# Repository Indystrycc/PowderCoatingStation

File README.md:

# PowderCoatingStation
Small and simple powder coating station with filters and light for small scale production.

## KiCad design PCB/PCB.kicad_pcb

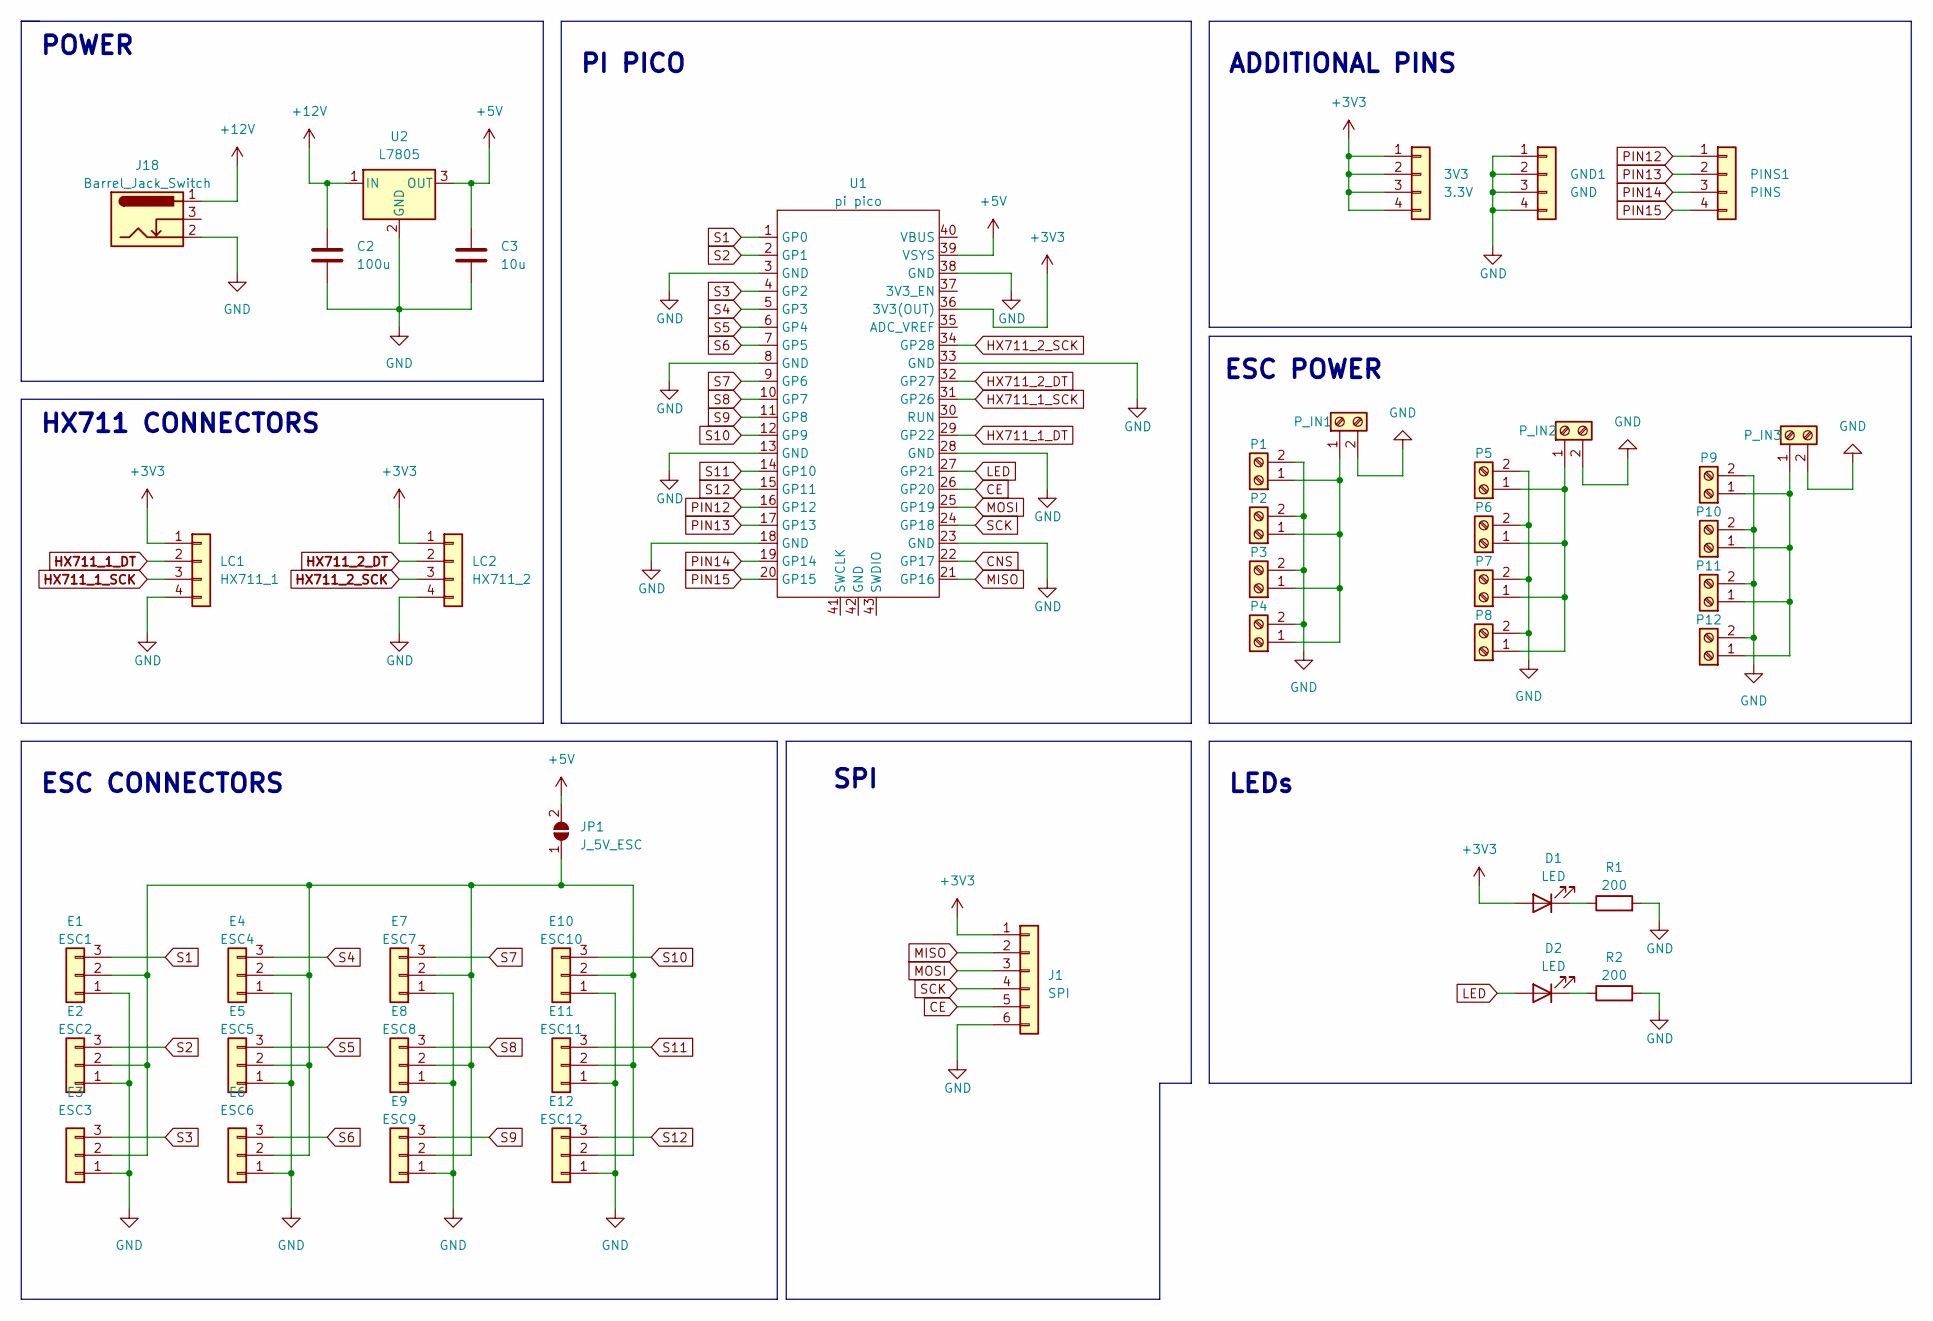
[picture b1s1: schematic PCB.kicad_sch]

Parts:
3V3: 3.3V; PinSocket_1x04_P2.54mm_Vertical
C2: 100u; C_Disc_D3.0mm_W2.0mm_P2.50mm
C3: 10u; C_Disc_D3.0mm_W2.0mm_P2.50mm
D1, D2: LED; LED_D5.0mm
E1: ESC1; PinSocket_1x03_P2.54mm_Vertical
E2: ESC2; PinSocket_1x03_P2.54mm_Vertical
E3: ESC3; PinSocket_1x03_P2.54mm_Vertical
E4: ESC4; PinSocket_1x03_P2.54mm_Vertical
E5: ESC5; PinSocket_1x03_P2.54mm_Vertical
E6: ESC6; PinSocket_1x03_P2.54mm_Vertical
E7: ESC7; PinSocket_1x03_P2.54mm_Vertical
E8: ESC8; PinSocket_1x03_P2.54mm_Vertical
E9: ESC9; PinSocket_1x03_P2.54mm_Vertical
E10: ESC10; PinSocket_1x03_P2.54mm_Vertical
E11: ESC11; PinSocket_1x03_P2.54mm_Vertical
E12: ESC12; PinSocket_1x03_P2.54mm_Vertical
GND1: GND; PinSocket_1x04_P2.54mm_Vertical
J1: SPI; PinSocket_1x06_P2.54mm_Vertical
J18: Barrel_Jack_Switch; BarrelJack_Horizontal
JP1: J_5V_ESC; SolderJumper-2_P1.3mm_Open_RoundedPad1.0x1.5mm
LC1: HX711_1; PinSocket_1x04_P2.54mm_Vertical
LC2: HX711_2; PinSocket_1x04_P2.54mm_Vertical
P1, P2, P3, P4, P5, P6, P7, P8, P9, P10, P11, P12: P1; TerminalBlock_bornier-2_P5.08mm
PINS1: PINS; PinSocket_1x04_P2.54mm_Vertical
P_IN1, P_IN2, P_IN3: P; TerminalBlock_bornier-2_P5.08mm
R1, R2: 200; R_0603_1608Metric_Pad0.98x0.95mm_HandSolder
U1: pi pico; raspberry pi pico
U2: L7805; TO-220-3_Vertical

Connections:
+3V3: 3V3.1, 3V3.2, 3V3.3, 3V3.4, D1.2 (A), J1.1, LC1.1, LC2.1, U1.36 (3V3(OUT))
CE: J1.5, U1.26 (GP20)
CNS: U1.22 (GP17)
GND: C2.2, E1.1, E2.1, E3.1, E4.1, E5.1, E6.1, E7.1, E8.1, E9.1, E10.1, E11.1, E12.1, GND1.1, GND1.2, GND1.3, GND1.4, J1.6, J18.2, LC1.4, LC2.4, P1.2, P2.2, P3.2, P4.2, P5.2, P6.2, P7.2, P8.2, P9.2, P10.2, P11.2, P12.2, P_IN1.2, P_IN2.2, P_IN3.2, R1.2, R2.2, U1.3 (GND), U1.8 (GND), U1.13 (GND), U1.18 (GND), U1.23 (GND), U1.28 (GND), U1.33 (GND), U1.38 (GND), U2.2 (GND); also elsewhere on the board
HX711_1_DT: LC1.2, U1.29 (GP22)
HX711_1_SCK: LC1.3, U1.31 (GP26)
HX711_2_DT: LC2.2, U1.32 (GP27)
HX711_2_SCK: LC2.3, U1.34 (GP28)
LED: D2.2 (A), U1.27 (GP21)
MISO: J1.2, U1.21 (GP16)
MOSI: J1.3, U1.25 (GP19)
unnamed: D1.1 (K), R1.1
unnamed: D2.1 (K), R2.1
unnamed: E1.2, E2.2, E3.2, E4.2, E5.2, E6.2, E7.2, E8.2, E9.2, E10.2, E11.2, E12.2, JP1.1 (A)
unnamed: P1.1, P2.1, P3.1, P4.1, P_IN1.1
unnamed: P5.1, P6.1, P7.1, P8.1, P_IN2.1
unnamed: P9.1, P10.1, P11.1, P12.1, P_IN3.1
PIN12: PINS1.1, U1.16 (GP12)
PIN13: PINS1.2, U1.17 (GP13)
PIN14: PINS1.3, U1.19 (GP14)
PIN15: PINS1.4, U1.20 (GP15)
S1: E1.3, U1.1 (GP0)
S2: E2.3, U1.2 (GP1)
S3: E3.3, U1.4 (GP2)
S4: E4.3, U1.5 (GP3)
S5: E5.3, U1.6 (GP4)
S6: E6.3, U1.7 (GP5)
S7: E7.3, U1.9 (GP6)
S8: E8.3, U1.10 (GP7)
S9: E9.3, U1.11 (GP8)
S10: E10.3, U1.12 (GP9)
S11: E11.3, U1.14 (GP10)
S12: E12.3, U1.15 (GP11)
SCK: J1.4, U1.24 (GP18)

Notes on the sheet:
ESC CONNECTORS
LEDs
ADDITIONAL PINS
SPI
ESC POWER
HX711 CONNECTORS
PI PICO
POWER

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
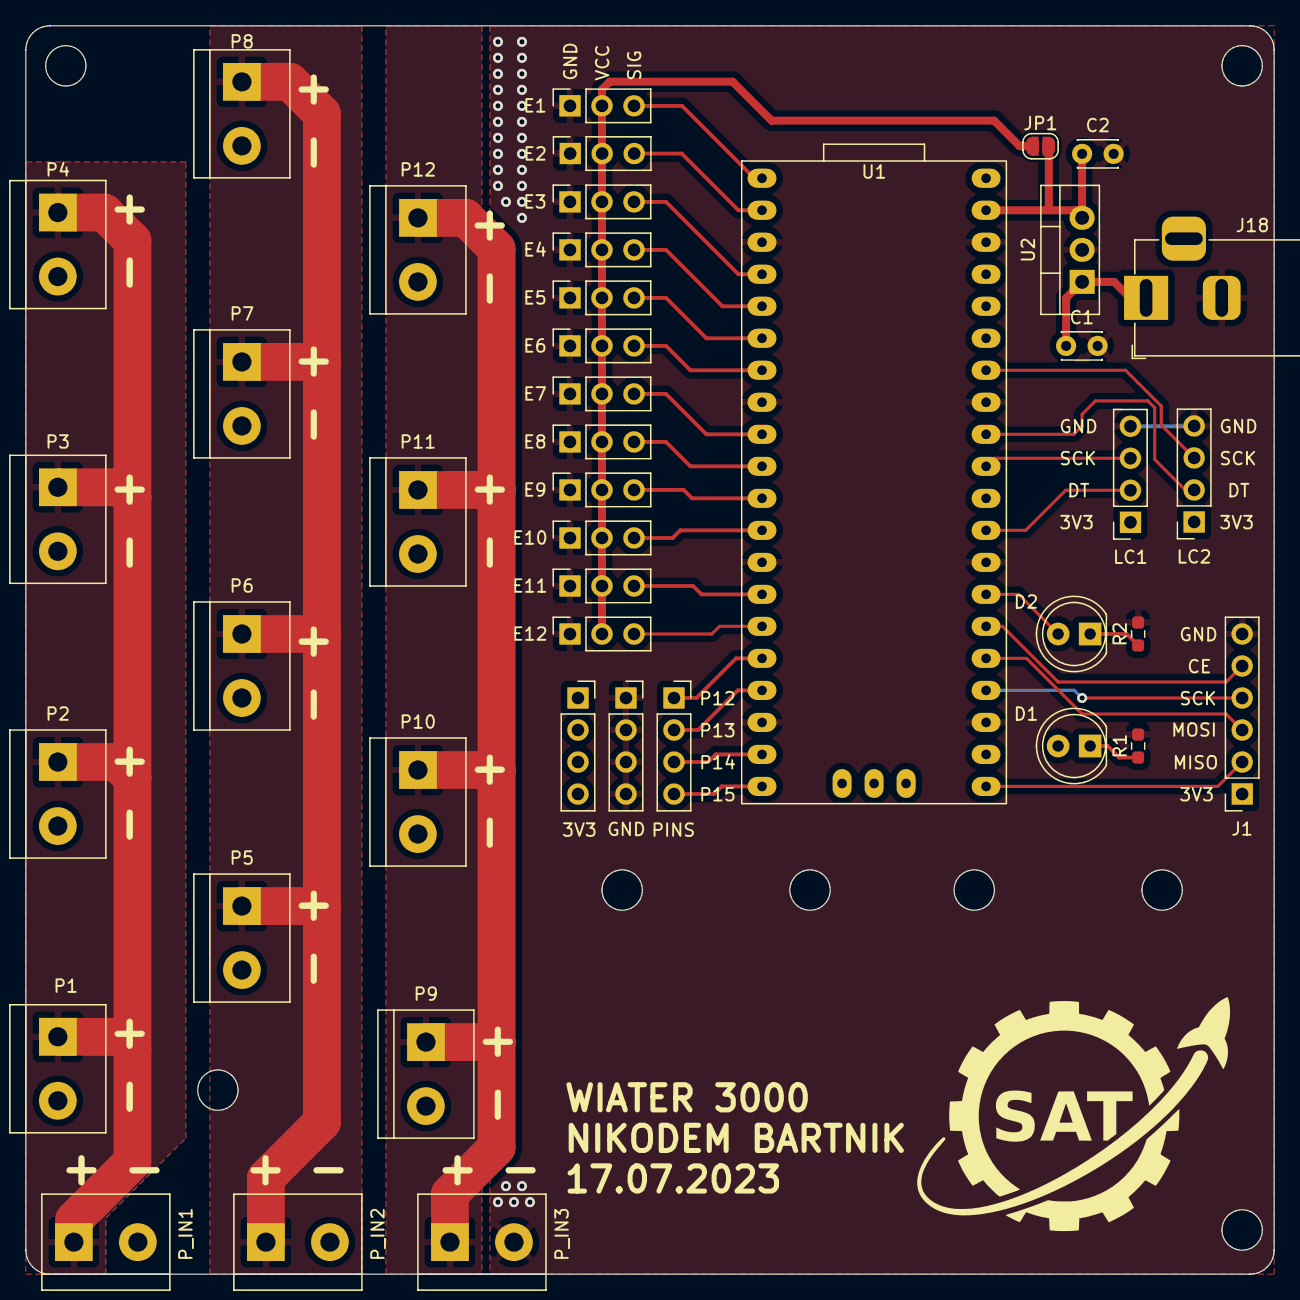
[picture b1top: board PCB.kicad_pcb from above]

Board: 2 copper layers, 99.1 x 99.1 mm, 43 parts (0 on the bottom side), 35 nets.

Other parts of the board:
C1: 100u; C_Disc_D3.0mm_W2.0mm_P2.50mm

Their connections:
GND: C1.2; also elsewhere on the board

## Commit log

2023-07-17 add schematic
2023-07-17 add PCB layout design
2023-07-18 fix and add production files
